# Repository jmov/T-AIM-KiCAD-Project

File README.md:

# t-aim-kicad
KiCAD project files for T-AIM device, Embedded Systems Project course 2017

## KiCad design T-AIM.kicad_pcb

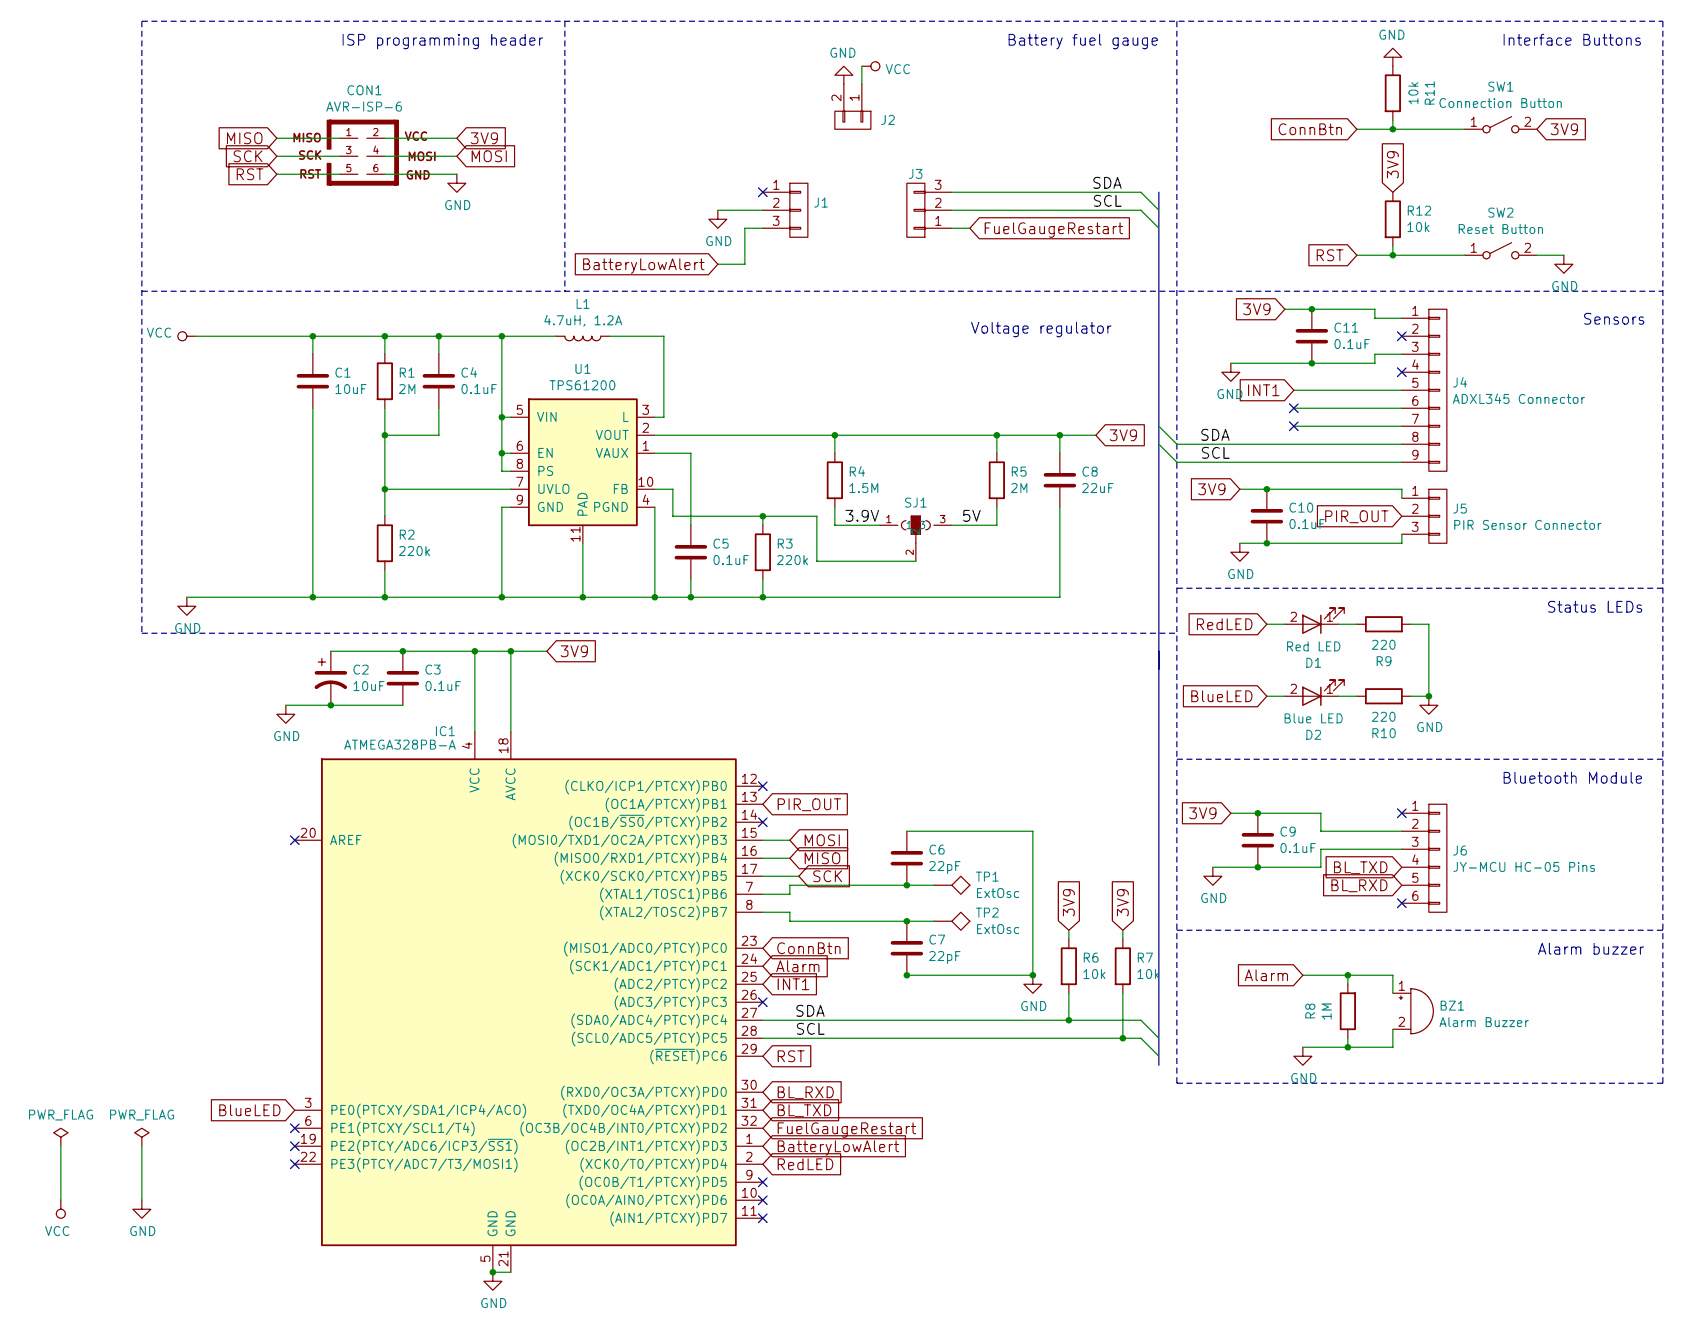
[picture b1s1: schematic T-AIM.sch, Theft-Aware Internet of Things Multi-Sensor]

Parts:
BZ1: Alarm Buzzer; AT-1220-TT-9-R
C1: 10uF; C_1206_HandSoldering
C2: 10uF; CP_Elec_5x5.3
C3, C4, C5, C9, C10, C11: 0.1uF; C_1206_HandSoldering
C6, C7: 22pF; C_0603_HandSoldering
C8: 22uF; C_1206_HandSoldering
CON1: AVR-ISP-6; 2X3-SHROUDED
D1: Red LED; LED_1206
D2: Blue LED; LED_1206
IC1: ATMEGA328PB-A; TQFP-32_7x7mm_Pitch0.8mm
J1, J3: CONN_01X03; Pin_Header_Straight_1x03_Pitch2.54mm
J2: CONN_01X02; Pin_Header_Straight_1x02_Pitch2.54mm
J4: ADXL345 Connector; Pin_Header_Straight_1x09_Pitch2.54mm
J5: PIR Sensor Connector; TO-5-3
J6: JY-MCU HC-05 Pins; Pin_Header_Straight_1x06_Pitch2.54mm
L1: 4.7uH, 1.2A; INDUCTOR_4.7UH
R1, R5: 2M; R_0805_HandSoldering
R2, R3: 220k; R_0805_HandSoldering
R4: 1.5M; R_0805_HandSoldering
R6, R7, R11, R12: 10k; R_1206_HandSoldering
R8: 1M; R_0805_HandSoldering
R9, R10: 220; R_1206_HandSoldering
SJ1: SOLDERJUMPER_2WAY-OLDPASTE1&2; SJ_3
SW1: Connection Button; SW_SPST_PTS645
SW2: Reset Button; SW_SPST_PTS645
TP1, TP2: ExtOsc; Pin_Header_Straight_1x01_Pitch2.54mm
U1: TPS61200; DRC-10-Thermal-Vias

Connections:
3V9: C2.1, C3.1, C8.1, C9.1, C10.1, C11.1, CON1.2, IC1.4 (VCC), IC1.18 (AVCC), J4.1, J5.1, J6.2, R4.1, R5.1, R6.1, R7.1, R12.1, SW1.2 (B), U1.2 (VOUT)
/3.9V: R4.2, SJ1.1
/5V: R5.2, SJ1.3
/SCL: IC1.28 ((SCL0/ADC5/PTCY)PC5), J3.2, J4.9, R7.2
/SDA: IC1.27 ((SDA0/ADC4/PTCY)PC4), J3.3, J4.8, R6.2
Alarm: BZ1.1 (-), IC1.24 ((SCK1/ADC1/PTCY)PC1), R8.2
BL_RXD: IC1.30 ((RXD0/OC3A/PTCXY)PD0), J6.5
BL_TXD: IC1.31 ((TXD0/OC4A/PTCXY)PD1), J6.4
BatteryLowAlert: IC1.1 ((OC2B/INT1/PTCXY)PD3), J1.3
BlueLED: D2.2 (A), IC1.3 (PE0(PTCXY/SDA1/ICP4/ACO))
ConnBtn: IC1.23 ((MISO1/ADC0/PTCY)PC0), R11.2, SW1.1 (A)
FuelGaugeRestart: IC1.32 ((OC3B/OC4B/INT0/PTCXY)PD2), J3.1
GND: BZ1.2 (+), C1.2, C2.2, C3.2, C5.2, C6.1, C7.2, C8.2, C9.2, C10.2, C11.2, CON1.6, IC1.5 (GND), IC1.21 (GND), J1.2, J2.2, J4.3, J5.3, J6.3, R2.2, R3.2, R8.1, R9.2, R10.2, R11.1, SW2.2 (B), U1.4 (PGND), U1.9 (GND), U1.11 (PAD)
INT1: IC1.25 ((ADC2/PTCY)PC2), J4.5
MISO: CON1.1, IC1.16 ((MISO0/RXD1/PTCXY)PB4)
MOSI: CON1.4, IC1.15 ((MOSI0/TXD1/OC2A/PTCXY)PB3)
unnamed: C4.2, R1.2, R2.1, U1.7 (UVLO)
unnamed: C5.1, U1.1 (VAUX)
unnamed: C6.2, IC1.7 ((XTAL1/TOSC1)PB6), TP1.1
unnamed: C7.1, IC1.8 ((XTAL2/TOSC2)PB7), TP2.1
unnamed: D1.1 (K), R9.1
unnamed: D2.1 (K), R10.1
unnamed: L1.1, U1.3 (L)
unnamed: R3.1, SJ1.2, U1.10 (FB)
PIR_OUT: IC1.13 ((OC1A/PTCXY)PB1), J5.2
RST: CON1.5, IC1.29 ((~RESET~)PC6), R12.2, SW2.1 (A)
RedLED: D1.2 (A), IC1.2 ((XCK0/T0/PTCXY)PD4)
SCK: CON1.3, IC1.17 ((XCK0/SCK0/PTCXY)PB5)
VCC: C1.1, C4.1, J2.1, L1.2, R1.1, U1.5 (VIN), U1.6 (EN), U1.8 (PS)

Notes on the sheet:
Status LEDs
Bluetooth Module
Interface Buttons
Sensors
Alarm buzzer
Battery fuel gauge
Voltage regulator
ISP programming header

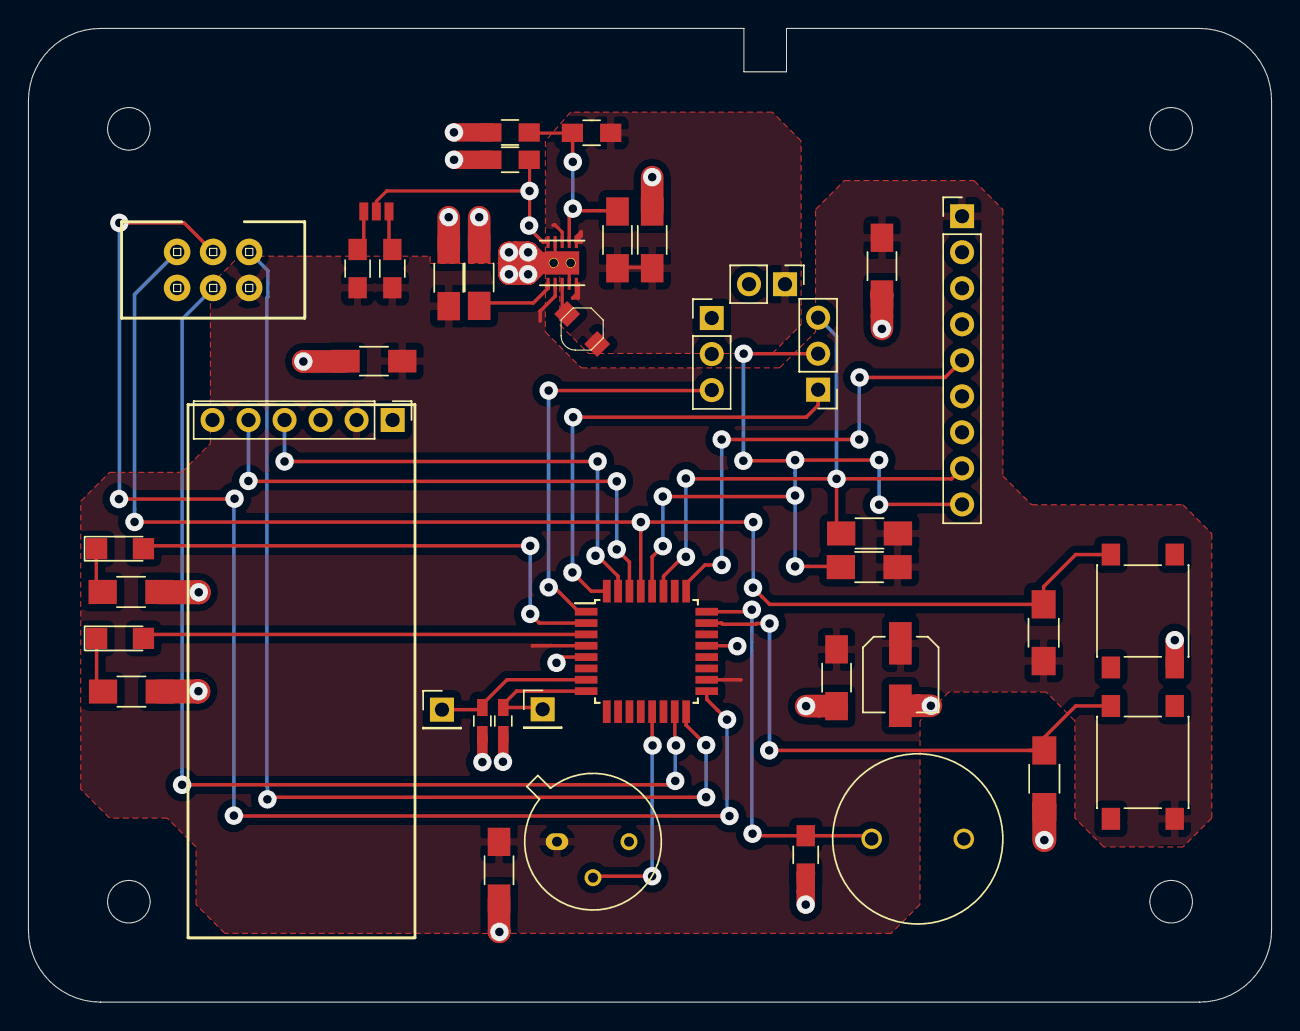
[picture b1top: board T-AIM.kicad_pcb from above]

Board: 2 copper layers, 87.7 x 68.7 mm, 45 parts (0 on the bottom side), 29 nets.

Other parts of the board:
S**: Screw_Hole_3_mm
S**#2, S**#3, S**#4: Screw_Hole_3_mm

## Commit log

2017-02-27 Schematics (WIP)
2017-02-27 Components wired
2017-02-28 Schematics tidied up, added Vcc caps in front of MCU
2017-02-28 Block name added
2017-03-01 Battery charger chip added to schematics
2017-03-01 Additional notes about battery hacking
2017-03-11 Regulator changed from linear to switching one
2017-03-16 Schematic switches changed; PCB footprints assigned; Preliminary PCB layout set
2017-03-17 Layout started
2017-03-17 Libraries added
2017-03-17 Adding tm-kicad-library
2017-03-17 Cleaned up the library
2017-03-17 Again, some library fixes
2017-03-17 Updating FetchYourself.txt
2017-03-17 Updating FetchYourself.txt again
2017-03-17 Hopefully final edit to FetchYourself.txt
2017-03-18 Components placed to layout
2017-03-20 First complete layout
2017-03-30 PCB rebuilt
2017-03-30 Test text added
2017-03-30 Schematic updated for 3.7V; Changed Buzzer resistor to 1M; PCB updated for SF LiPo Gauge; Gerbers generated
2017-03-31 Updated TPS61200 Thermal Pad, PCB Layout and Gerbers; Slightly edited schematics
2017-05-08 v0.3: 3.9V field shrunk; Added ISP header; Fixed fuel gauge pin shortcut :P
2017-05-08 v0.3 from 3.7V branch merged to master
2017-05-12 T-AIM v0.3 Final? (Hah): Fixed a C9 footprint from 1210 -> 1206; Updated the script in Gerbers directory to add copper markings (Try script first in command line with -h/--help parameter)
